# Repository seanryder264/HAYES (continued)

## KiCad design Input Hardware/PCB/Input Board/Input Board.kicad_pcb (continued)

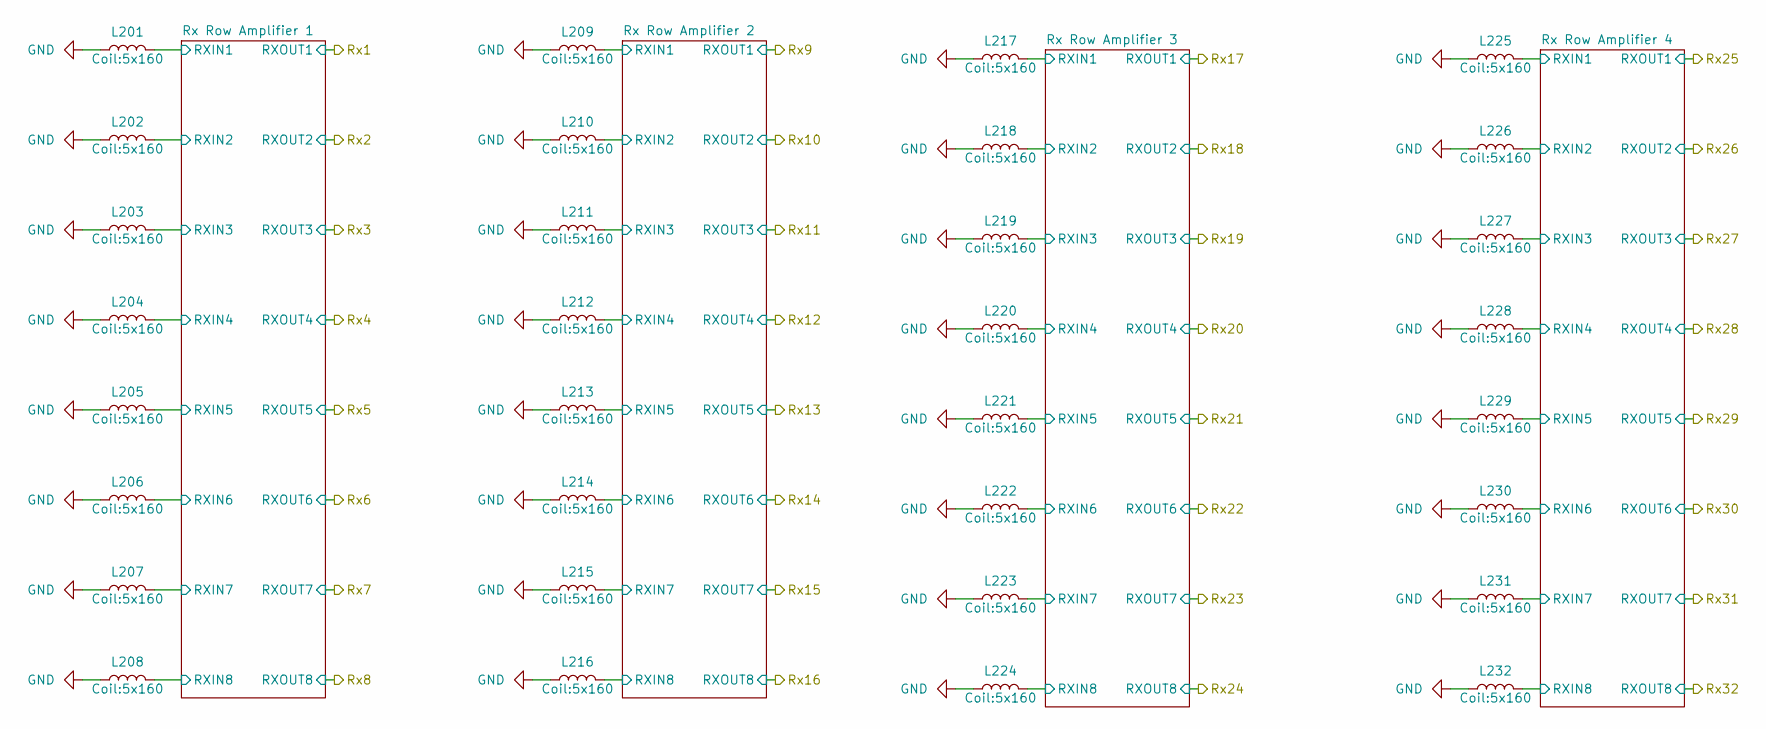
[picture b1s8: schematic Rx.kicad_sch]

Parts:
L201, L202, L203, L204, L205, L206, L207, L208, L209, L210, L211, L212, L213, L214, L215, L216, L217, L218, L219, L220, L221, L222, L223, L224, L225, L226, L227, L228, L229, L230, L231, L232: L; 5x160

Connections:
/Receiver Stage/Rx Row Amplifier 1/RXIN1: L201.2; also elsewhere on the board
/Receiver Stage/Rx Row Amplifier 1/RXIN2: L202.2; also elsewhere on the board
/Receiver Stage/Rx Row Amplifier 1/RXIN3: L203.2; also elsewhere on the board
/Receiver Stage/Rx Row Amplifier 1/RXIN4: L204.2; also elsewhere on the board
/Receiver Stage/Rx Row Amplifier 1/RXIN5: L205.2; also elsewhere on the board
/Receiver Stage/Rx Row Amplifier 1/RXIN6: L206.2; also elsewhere on the board
/Receiver Stage/Rx Row Amplifier 1/RXIN7: L207.2; also elsewhere on the board
/Receiver Stage/Rx Row Amplifier 1/RXIN8: L208.2; also elsewhere on the board
/Receiver Stage/Rx Row Amplifier 2/RXIN1: L209.2; also elsewhere on the board
/Receiver Stage/Rx Row Amplifier 2/RXIN2: L210.2; also elsewhere on the board
/Receiver Stage/Rx Row Amplifier 2/RXIN3: L211.2; also elsewhere on the board
/Receiver Stage/Rx Row Amplifier 2/RXIN4: L212.2; also elsewhere on the board
/Receiver Stage/Rx Row Amplifier 2/RXIN5: L213.2; also elsewhere on the board
/Receiver Stage/Rx Row Amplifier 2/RXIN6: L214.2; also elsewhere on the board
/Receiver Stage/Rx Row Amplifier 2/RXIN7: L215.2; also elsewhere on the board
/Receiver Stage/Rx Row Amplifier 2/RXIN8: L216.2; also elsewhere on the board
/Receiver Stage/Rx Row Amplifier 3/RXIN1: L217.2; also elsewhere on the board
/Receiver Stage/Rx Row Amplifier 3/RXIN2: L218.2; also elsewhere on the board
/Receiver Stage/Rx Row Amplifier 3/RXIN3: L219.2; also elsewhere on the board
/Receiver Stage/Rx Row Amplifier 3/RXIN4: L220.2; also elsewhere on the board
/Receiver Stage/Rx Row Amplifier 3/RXIN5: L221.2; also elsewhere on the board
/Receiver Stage/Rx Row Amplifier 3/RXIN6: L222.2; also elsewhere on the board
/Receiver Stage/Rx Row Amplifier 3/RXIN7: L223.2; also elsewhere on the board
/Receiver Stage/Rx Row Amplifier 3/RXIN8: L224.2; also elsewhere on the board
/Receiver Stage/Rx Row Amplifier 4/RXIN1: L225.2; also elsewhere on the board
/Receiver Stage/Rx Row Amplifier 4/RXIN2: L226.2; also elsewhere on the board
/Receiver Stage/Rx Row Amplifier 4/RXIN3: L227.2; also elsewhere on the board
/Receiver Stage/Rx Row Amplifier 4/RXIN4: L228.2; also elsewhere on the board
/Receiver Stage/Rx Row Amplifier 4/RXIN5: L229.2; also elsewhere on the board
/Receiver Stage/Rx Row Amplifier 4/RXIN6: L230.2; also elsewhere on the board
/Receiver Stage/Rx Row Amplifier 4/RXIN7: L231.2; also elsewhere on the board
/Receiver Stage/Rx Row Amplifier 4/RXIN8: L232.2; also elsewhere on the board

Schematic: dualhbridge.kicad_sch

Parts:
C1101, C1102, C1103, C1104, C1105: 100n; C_0603_1608Metric
U1101: 74HCS95; DHVQFN-16-1EP_2.5x3.5mm_P0.5mm_EP1x2mm
U1102, U1103, U1104, U1105: DRV8837; WSON-8-1EP_2x2mm_P0.5mm_EP0.9x1.6mm

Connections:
+5V: C1101.2, C1102.2, C1103.2, C1104.2, C1105.2, U1101.10 (~SRCLR), U1101.16 (VCC), U1102.1 (VM), U1102.8 (VCC), U1103.1 (VM), U1103.8 (VCC), U1104.1 (VM), U1104.8 (VCC), U1105.1 (VM), U1105.8 (VCC); also elsewhere on the board
/Measurement & Control/TX_RCLK: U1101.12 (RCLK); also elsewhere on the board
/Measurement & Control/TX_SDO: U1101.14 (SER); also elsewhere on the board
/Measurement & Control/TX_SRCLK: U1101.11 (SRCLK); also elsewhere on the board
/Transmit Coils/Dual H-Bridge 1/OUT1: U1102.2 (OUT1); also elsewhere on the board
/Transmit Coils/Dual H-Bridge 1/OUT2: U1102.3 (OUT2); also elsewhere on the board
/Transmit Coils/Dual H-Bridge 1/OUT3: U1103.2 (OUT1); also elsewhere on the board
/Transmit Coils/Dual H-Bridge 1/OUT4: U1103.3 (OUT2); also elsewhere on the board
/Transmit Coils/Dual H-Bridge 1/OUT5: U1104.2 (OUT1); also elsewhere on the board
/Transmit Coils/Dual H-Bridge 1/OUT6: U1104.3 (OUT2); also elsewhere on the board
/Transmit Coils/Dual H-Bridge 1/OUT7: U1105.2 (OUT1); also elsewhere on the board
/Transmit Coils/Dual H-Bridge 1/OUT8: U1105.3 (OUT2); also elsewhere on the board
/Transmit Coils/Dual H-Bridge 1/QH': U1101.9 (QH'); also elsewhere on the board
unnamed: U1101.15 (QA), U1102.6 (IN1)
unnamed: U1101.1 (QB), U1102.5 (IN2)
unnamed: U1101.2 (QC), U1103.6 (IN1)
unnamed: U1101.3 (QD), U1103.5 (IN2)
unnamed: U1101.4 (QE), U1104.6 (IN1)
unnamed: U1101.5 (QF), U1104.5 (IN2)
unnamed: U1101.6 (QG), U1105.6 (IN1)
unnamed: U1101.7 (QH), U1105.5 (IN2)

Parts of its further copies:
C1201, C1202, C1203, C1204, C1205, C1301, C1302, C1303, C1304, C1305, C1401, C1402, C1403, C1404, C1405: 100n; C_0603_1608Metric
U1201, U1301, U1401: 74HCS95; DHVQFN-16-1EP_2.5x3.5mm_P0.5mm_EP1x2mm
U1202, U1203, U1204, U1205, U1302, U1303, U1304, U1305, U1402, U1403, U1404, U1405: DRV8837; WSON-8-1EP_2x2mm_P0.5mm_EP0.9x1.6mm

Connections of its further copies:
+5V: C1201.2, C1202.2, C1203.2, C1204.2, C1205.2, C1301.2, C1302.2, C1303.2, C1304.2, C1305.2, C1401.2, C1402.2, C1403.2, C1404.2, C1405.2, U1201.10 (~SRCLR), U1201.16 (VCC), U1202.1 (VM), U1202.8 (VCC), U1203.1 (VM), U1203.8 (VCC), U1204.1 (VM), U1204.8 (VCC), U1205.1 (VM), U1205.8 (VCC), U1301.10 (~SRCLR), U1301.16 (VCC), U1302.1 (VM), U1302.8 (VCC), U1303.1 (VM), U1303.8 (VCC), U1304.1 (VM), U1304.8 (VCC), U1305.1 (VM), U1305.8 (VCC), U1401.10 (~SRCLR), U1401.16 (VCC), U1402.1 (VM), U1402.8 (VCC), U1403.1 (VM), U1403.8 (VCC), U1404.1 (VM), U1404.8 (VCC), U1405.1 (VM), U1405.8 (VCC); also elsewhere on the board
/Measurement & Control/TX_RCLK: U1201.12 (RCLK), U1301.12 (RCLK), U1401.12 (RCLK); also elsewhere on the board
/Measurement & Control/TX_SRCLK: U1201.11 (SRCLK), U1301.11 (SRCLK), U1401.11 (SRCLK); also elsewhere on the board
/Transmit Coils/Dual H-Bridge 1/QH': U1201.14 (SER); also elsewhere on the board
/Transmit Coils/Dual H-Bridge 2/OUT1: U1202.2 (OUT1); also elsewhere on the board
/Transmit Coils/Dual H-Bridge 2/OUT2: U1202.3 (OUT2); also elsewhere on the board
/Transmit Coils/Dual H-Bridge 2/OUT3: U1203.2 (OUT1); also elsewhere on the board
/Transmit Coils/Dual H-Bridge 2/OUT4: U1203.3 (OUT2); also elsewhere on the board
/Transmit Coils/Dual H-Bridge 2/OUT5: U1204.2 (OUT1); also elsewhere on the board
/Transmit Coils/Dual H-Bridge 2/OUT6: U1204.3 (OUT2); also elsewhere on the board
/Transmit Coils/Dual H-Bridge 2/OUT7: U1205.2 (OUT1); also elsewhere on the board
/Transmit Coils/Dual H-Bridge 2/OUT8: U1205.3 (OUT2); also elsewhere on the board
/Transmit Coils/Dual H-Bridge 3/OUT1: U1302.2 (OUT1); also elsewhere on the board
/Transmit Coils/Dual H-Bridge 3/OUT2: U1302.3 (OUT2); also elsewhere on the board
/Transmit Coils/Dual H-Bridge 3/OUT3: U1303.2 (OUT1); also elsewhere on the board
/Transmit Coils/Dual H-Bridge 3/OUT4: U1303.3 (OUT2); also elsewhere on the board
/Transmit Coils/Dual H-Bridge 3/OUT5: U1304.2 (OUT1); also elsewhere on the board
/Transmit Coils/Dual H-Bridge 3/OUT6: U1304.3 (OUT2); also elsewhere on the board
/Transmit Coils/Dual H-Bridge 3/OUT7: U1305.2 (OUT1); also elsewhere on the board
/Transmit Coils/Dual H-Bridge 3/OUT8: U1305.3 (OUT2); also elsewhere on the board
/Transmit Coils/Dual H-Bridge 3/QH': U1301.9 (QH'), U1401.14 (SER)
/Transmit Coils/Dual H-Bridge 4/OUT1: U1402.2 (OUT1); also elsewhere on the board
/Transmit Coils/Dual H-Bridge 4/OUT2: U1402.3 (OUT2); also elsewhere on the board
/Transmit Coils/Dual H-Bridge 4/OUT3: U1403.2 (OUT1); also elsewhere on the board
/Transmit Coils/Dual H-Bridge 4/OUT4: U1403.3 (OUT2); also elsewhere on the board
/Transmit Coils/Dual H-Bridge 4/OUT5: U1404.2 (OUT1); also elsewhere on the board
/Transmit Coils/Dual H-Bridge 4/OUT6: U1404.3 (OUT2); also elsewhere on the board
/Transmit Coils/Dual H-Bridge 4/OUT7: U1405.2 (OUT1); also elsewhere on the board
/Transmit Coils/Dual H-Bridge 4/OUT8: U1405.3 (OUT2); also elsewhere on the board
/Transmit Coils/Dual H-Bridge 4/QH&apos;: U1401.9 (QH')
/Transmit Coils/QH': U1201.9 (QH'), U1301.14 (SER)
unnamed: U1201.15 (QA), U1202.6 (IN1)
unnamed: U1201.1 (QB), U1202.5 (IN2)
unnamed: U1201.2 (QC), U1203.6 (IN1)
unnamed: U1201.3 (QD), U1203.5 (IN2)
unnamed: U1201.4 (QE), U1204.6 (IN1)
unnamed: U1201.5 (QF), U1204.5 (IN2)
unnamed: U1201.6 (QG), U1205.6 (IN1)
unnamed: U1201.7 (QH), U1205.5 (IN2)
unnamed: U1301.15 (QA), U1302.6 (IN1)
unnamed: U1301.1 (QB), U1302.5 (IN2)
unnamed: U1301.2 (QC), U1303.6 (IN1)
unnamed: U1301.3 (QD), U1303.5 (IN2)
unnamed: U1301.4 (QE), U1304.6 (IN1)
unnamed: U1301.5 (QF), U1304.5 (IN2)
unnamed: U1301.6 (QG), U1305.6 (IN1)
unnamed: U1301.7 (QH), U1305.5 (IN2)
unnamed: U1401.15 (QA), U1402.6 (IN1)
unnamed: U1401.1 (QB), U1402.5 (IN2)
unnamed: U1401.2 (QC), U1403.6 (IN1)
unnamed: U1401.3 (QD), U1403.5 (IN2)
unnamed: U1401.4 (QE), U1404.6 (IN1)
unnamed: U1401.5 (QF), U1404.5 (IN2)
unnamed: U1401.6 (QG), U1405.6 (IN1)
unnamed: U1401.7 (QH), U1405.5 (IN2)

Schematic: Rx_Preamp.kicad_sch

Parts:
C301, C302, C303, C304, C306, C307, C309, C310, C311, C312, C313, C314, C315, C316, C317, C318: 1.8n; C_0603_1608Metric
C305, C308: 100n; C_0603_1608Metric
R301, R302, R303, R304, R307, R308, R309, R310, R313, R314, R315, R316, R319, R320, R321, R322: 1k; R_0603_1608Metric
R305, R306, R311, R312, R317, R318, R323, R324: 15k; R_0603_1608Metric
U301, U302: TSV994; SOIC-14_3.9x8.7mm_P1.27mm

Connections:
1.65V: C303.2, C304.2, C309.2, C310.2, C313.2, C314.2, C317.2, C318.2, R301.1, R302.1, R307.1, R308.1, R313.1, R314.1, R319.1, R320.1; also elsewhere on the board
+3.3VA: C305.1, C308.1, U301.4 (V+), U302.4 (V+); also elsewhere on the board
/Mux & Amplifier 1/In1: R305.2, U301.1; also elsewhere on the board
/Mux & Amplifier 1/In2: R306.2, U301.7; also elsewhere on the board
/Mux & Amplifier 1/In3: R311.2, U301.8; also elsewhere on the board
/Mux & Amplifier 1/In4: R312.2, U301.14; also elsewhere on the board
/Mux & Amplifier 1/In5: R317.2, U302.1; also elsewhere on the board
/Mux & Amplifier 1/In6: R318.2, U302.7; also elsewhere on the board
/Mux & Amplifier 1/In7: R323.2, U302.8; also elsewhere on the board
/Mux & Amplifier 1/In8: R324.2, U302.14; also elsewhere on the board
/Receiver Stage/Rx Row Amplifier 1/RXIN1: C301.2; also elsewhere on the board
/Receiver Stage/Rx Row Amplifier 1/RXIN2: C302.2; also elsewhere on the board
/Receiver Stage/Rx Row Amplifier 1/RXIN3: C306.2; also elsewhere on the board
/Receiver Stage/Rx Row Amplifier 1/RXIN4: C307.2; also elsewhere on the board
/Receiver Stage/Rx Row Amplifier 1/RXIN5: C311.2; also elsewhere on the board
/Receiver Stage/Rx Row Amplifier 1/RXIN6: C312.2; also elsewhere on the board
/Receiver Stage/Rx Row Amplifier 1/RXIN7: C315.2; also elsewhere on the board
/Receiver Stage/Rx Row Amplifier 1/RXIN8: C316.2; also elsewhere on the board
unnamed: C303.1, R303.2
unnamed: C304.1, R304.2
unnamed: C309.1, R309.2
unnamed: C310.1, R310.2
unnamed: C313.1, R315.2
unnamed: C314.1, R316.2
unnamed: C317.1, R321.2
unnamed: C318.1, R322.2
unnamed: C301.1, R301.2, U301.3 (+)
unnamed: R303.1, R305.1, U301.2 (-)
unnamed: C302.1, R302.2, U301.5 (+)
unnamed: R304.1, R306.1, U301.6 (-)
unnamed: C306.1, R307.2, U301.10 (+)
unnamed: R309.1, R311.1, U301.9 (-)
unnamed: C307.1, R308.2, U301.12 (+)
unnamed: R310.1, R312.1, U301.13 (-)
unnamed: C311.1, R313.2, U302.3 (+)
unnamed: R315.1, R317.1, U302.2 (-)
unnamed: C312.1, R314.2, U302.5 (+)
unnamed: R316.1, R318.1, U302.6 (-)
unnamed: C315.1, R319.2, U302.10 (+)
unnamed: R321.1, R323.1, U302.9 (-)
unnamed: C316.1, R320.2, U302.12 (+)
unnamed: R322.1, R324.1, U302.13 (-)

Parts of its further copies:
C401, C402, C403, C404, C406, C407, C409, C410, C411, C412, C413, C414, C415, C416, C417, C418, C501, C502, C503, C504, C506, C507, C509, C510, C511, C512, C513, C514, C515, C516, C517, C518, C601, C602, C603, C604, C606, C607, C609, C610, C611, C612, C613, C614, C615, C616, C617, C618: 1.8n; C_0603_1608Metric
C405, C408, C505, C508, C605, C608: 100n; C_0603_1608Metric
R401, R402, R403, R404, R407, R408, R409, R410, R413, R414, R415, R416, R419, R420, R421, R422, R501, R502, R503, R504, R507, R508, R509, R510, R513, R514, R515, R516, R519, R520, R521, R522, R601, R602, R603, R604, R607, R608, R609, R610, R613, R614, R615, R616, R619, R620, R621, R622: 1k; R_0603_1608Metric
R405, R406, R411, R412, R417, R418, R423, R424, R505, R506, R511, R512, R517, R518, R523, R524, R605, R606, R611, R612, R617, R618, R623, R624: 15k; R_0603_1608Metric
U401, U402, U501, U502, U601, U602: TSV994; SOIC-14_3.9x8.7mm_P1.27mm

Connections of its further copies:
1.65V: C403.2, C404.2, C409.2, C410.2, C413.2, C414.2, C417.2, C418.2, C503.2, C504.2, C509.2, C510.2, C513.2, C514.2, C517.2, C518.2, C603.2, C604.2, C609.2, C610.2, C613.2, C614.2, C617.2, C618.2, R401.1, R402.1, R407.1, R408.1, R413.1, R414.1, R419.1, R420.1, R501.1, R502.1, R507.1, R508.1, R513.1, R514.1, R519.1, R520.1, R601.1, R602.1, R607.1, R608.1, R613.1, R614.1, R619.1, R620.1; also elsewhere on the board
+3.3VA: C405.1, C408.1, C505.1, C508.1, C605.1, C608.1, U401.4 (V+), U402.4 (V+), U501.4 (V+), U502.4 (V+), U601.4 (V+), U602.4 (V+); also elsewhere on the board
/Mux & Amplifier 1/In9: R405.2, U401.1; also elsewhere on the board
/Mux & Amplifier 1/In10: R406.2, U401.7; also elsewhere on the board
/Mux & Amplifier 1/In11: R411.2, U401.8; also elsewhere on the board
/Mux & Amplifier 1/In12: R412.2, U401.14; also elsewhere on the board
/Mux & Amplifier 1/In13: R417.2, U402.1; also elsewhere on the board
/Mux & Amplifier 1/In14: R418.2, U402.7; also elsewhere on the board
/Mux & Amplifier 1/In15: R423.2, U402.8; also elsewhere on the board
/Mux & Amplifier 1/In16: R424.2, U402.14; also elsewhere on the board
/Mux & Amplifier 2/In1: R505.2, U501.1; also elsewhere on the board
/Mux & Amplifier 2/In2: R506.2, U501.7; also elsewhere on the board
/Mux & Amplifier 2/In3: R511.2, U501.8; also elsewhere on the board
/Mux & Amplifier 2/In4: R512.2, U501.14; also elsewhere on the board
/Mux & Amplifier 2/In5: R517.2, U502.1; also elsewhere on the board
/Mux & Amplifier 2/In6: R518.2, U502.7; also elsewhere on the board
/Mux & Amplifier 2/In7: R523.2, U502.8; also elsewhere on the board
/Mux & Amplifier 2/In8: R524.2, U502.14; also elsewhere on the board
/Mux & Amplifier 2/In9: R605.2, U601.1; also elsewhere on the board
/Mux & Amplifier 2/In10: R606.2, U601.7; also elsewhere on the board
/Mux & Amplifier 2/In11: R611.2, U601.8; also elsewhere on the board
/Mux & Amplifier 2/In12: R612.2, U601.14; also elsewhere on the board
/Mux & Amplifier 2/In13: R617.2, U602.1; also elsewhere on the board
/Mux & Amplifier 2/In14: R618.2, U602.7; also elsewhere on the board
/Mux & Amplifier 2/In15: R623.2, U602.8; also elsewhere on the board
/Mux & Amplifier 2/In16: R624.2, U602.14; also elsewhere on the board
/Receiver Stage/Rx Row Amplifier 2/RXIN1: C401.2; also elsewhere on the board
/Receiver Stage/Rx Row Amplifier 2/RXIN2: C402.2; also elsewhere on the board
/Receiver Stage/Rx Row Amplifier 2/RXIN3: C406.2; also elsewhere on the board
/Receiver Stage/Rx Row Amplifier 2/RXIN4: C407.2; also elsewhere on the board
/Receiver Stage/Rx Row Amplifier 2/RXIN5: C411.2; also elsewhere on the board
/Receiver Stage/Rx Row Amplifier 2/RXIN6: C412.2; also elsewhere on the board
/Receiver Stage/Rx Row Amplifier 2/RXIN7: C415.2; also elsewhere on the board
/Receiver Stage/Rx Row Amplifier 2/RXIN8: C416.2; also elsewhere on the board
/Receiver Stage/Rx Row Amplifier 3/RXIN1: C501.2; also elsewhere on the board
/Receiver Stage/Rx Row Amplifier 3/RXIN2: C502.2; also elsewhere on the board
/Receiver Stage/Rx Row Amplifier 3/RXIN3: C506.2; also elsewhere on the board
/Receiver Stage/Rx Row Amplifier 3/RXIN4: C507.2; also elsewhere on the board
/Receiver Stage/Rx Row Amplifier 3/RXIN5: C511.2; also elsewhere on the board
/Receiver Stage/Rx Row Amplifier 3/RXIN6: C512.2; also elsewhere on the board
/Receiver Stage/Rx Row Amplifier 3/RXIN7: C515.2; also elsewhere on the board
/Receiver Stage/Rx Row Amplifier 3/RXIN8: C516.2; also elsewhere on the board
/Receiver Stage/Rx Row Amplifier 4/RXIN1: C601.2; also elsewhere on the board
/Receiver Stage/Rx Row Amplifier 4/RXIN2: C602.2; also elsewhere on the board
/Receiver Stage/Rx Row Amplifier 4/RXIN3: C606.2; also elsewhere on the board
/Receiver Stage/Rx Row Amplifier 4/RXIN4: C607.2; also elsewhere on the board
/Receiver Stage/Rx Row Amplifier 4/RXIN5: C611.2; also elsewhere on the board
/Receiver Stage/Rx Row Amplifier 4/RXIN6: C612.2; also elsewhere on the board
/Receiver Stage/Rx Row Amplifier 4/RXIN7: C615.2; also elsewhere on the board
/Receiver Stage/Rx Row Amplifier 4/RXIN8: C616.2; also elsewhere on the board
unnamed: C403.1, R403.2
unnamed: C404.1, R404.2
unnamed: C409.1, R409.2
unnamed: C410.1, R410.2
unnamed: C413.1, R415.2
unnamed: C414.1, R416.2
unnamed: C417.1, R421.2
unnamed: C418.1, R422.2
unnamed: C503.1, R503.2
unnamed: C504.1, R504.2
unnamed: C509.1, R509.2
unnamed: C510.1, R510.2
unnamed: C513.1, R515.2
unnamed: C514.1, R516.2
unnamed: C517.1, R521.2
unnamed: C518.1, R522.2
unnamed: C603.1, R603.2
unnamed: C604.1, R604.2
unnamed: C609.1, R609.2
unnamed: C610.1, R610.2
unnamed: C613.1, R615.2
unnamed: C614.1, R616.2
unnamed: C617.1, R621.2
unnamed: C618.1, R622.2
unnamed: C401.1, R401.2, U401.3 (+)
unnamed: R403.1, R405.1, U401.2 (-)
unnamed: C402.1, R402.2, U401.5 (+)
unnamed: R404.1, R406.1, U401.6 (-)
unnamed: C406.1, R407.2, U401.10 (+)
unnamed: R409.1, R411.1, U401.9 (-)
unnamed: C407.1, R408.2, U401.12 (+)
unnamed: R410.1, R412.1, U401.13 (-)
unnamed: C411.1, R413.2, U402.3 (+)
unnamed: R415.1, R417.1, U402.2 (-)
unnamed: C412.1, R414.2, U402.5 (+)
unnamed: R416.1, R418.1, U402.6 (-)
unnamed: C415.1, R419.2, U402.10 (+)
unnamed: R421.1, R423.1, U402.9 (-)
unnamed: C416.1, R420.2, U402.12 (+)
unnamed: R422.1, R424.1, U402.13 (-)
unnamed: C501.1, R501.2, U501.3 (+)
unnamed: R503.1, R505.1, U501.2 (-)
unnamed: C502.1, R502.2, U501.5 (+)
unnamed: R504.1, R506.1, U501.6 (-)
unnamed: C506.1, R507.2, U501.10 (+)
unnamed: R509.1, R511.1, U501.9 (-)
unnamed: C507.1, R508.2, U501.12 (+)
unnamed: R510.1, R512.1, U501.13 (-)
unnamed: C511.1, R513.2, U502.3 (+)
unnamed: R515.1, R517.1, U502.2 (-)
unnamed: C512.1, R514.2, U502.5 (+)
unnamed: R516.1, R518.1, U502.6 (-)
unnamed: C515.1, R519.2, U502.10 (+)
unnamed: R521.1, R523.1, U502.9 (-)
unnamed: C516.1, R520.2, U502.12 (+)
unnamed: R522.1, R524.1, U502.13 (-)
unnamed: C601.1, R601.2, U601.3 (+)
unnamed: R603.1, R605.1, U601.2 (-)
unnamed: C602.1, R602.2, U601.5 (+)
unnamed: R604.1, R606.1, U601.6 (-)
unnamed: C606.1, R607.2, U601.10 (+)
unnamed: R609.1, R611.1, U601.9 (-)
unnamed: C607.1, R608.2, U601.12 (+)
unnamed: R610.1, R612.1, U601.13 (-)
unnamed: C611.1, R613.2, U602.3 (+)
unnamed: R615.1, R617.1, U602.2 (-)
unnamed: C612.1, R614.2, U602.5 (+)
unnamed: R616.1, R618.1, U602.6 (-)
unnamed: C615.1, R619.2, U602.10 (+)
unnamed: R621.1, R623.1, U602.9 (-)
unnamed: C616.1, R620.2, U602.12 (+)
unnamed: R622.1, R624.1, U602.13 (-)

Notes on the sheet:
OPAMP NOT ALWAYS STABLE
TSV994
×17.7 @1MHz Gain slightly less to preserve bandwidth
This is almost certainly wrong look at the transfer functions also sims rely on a slight approximation of this opamp so may actually be completley incorrect

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
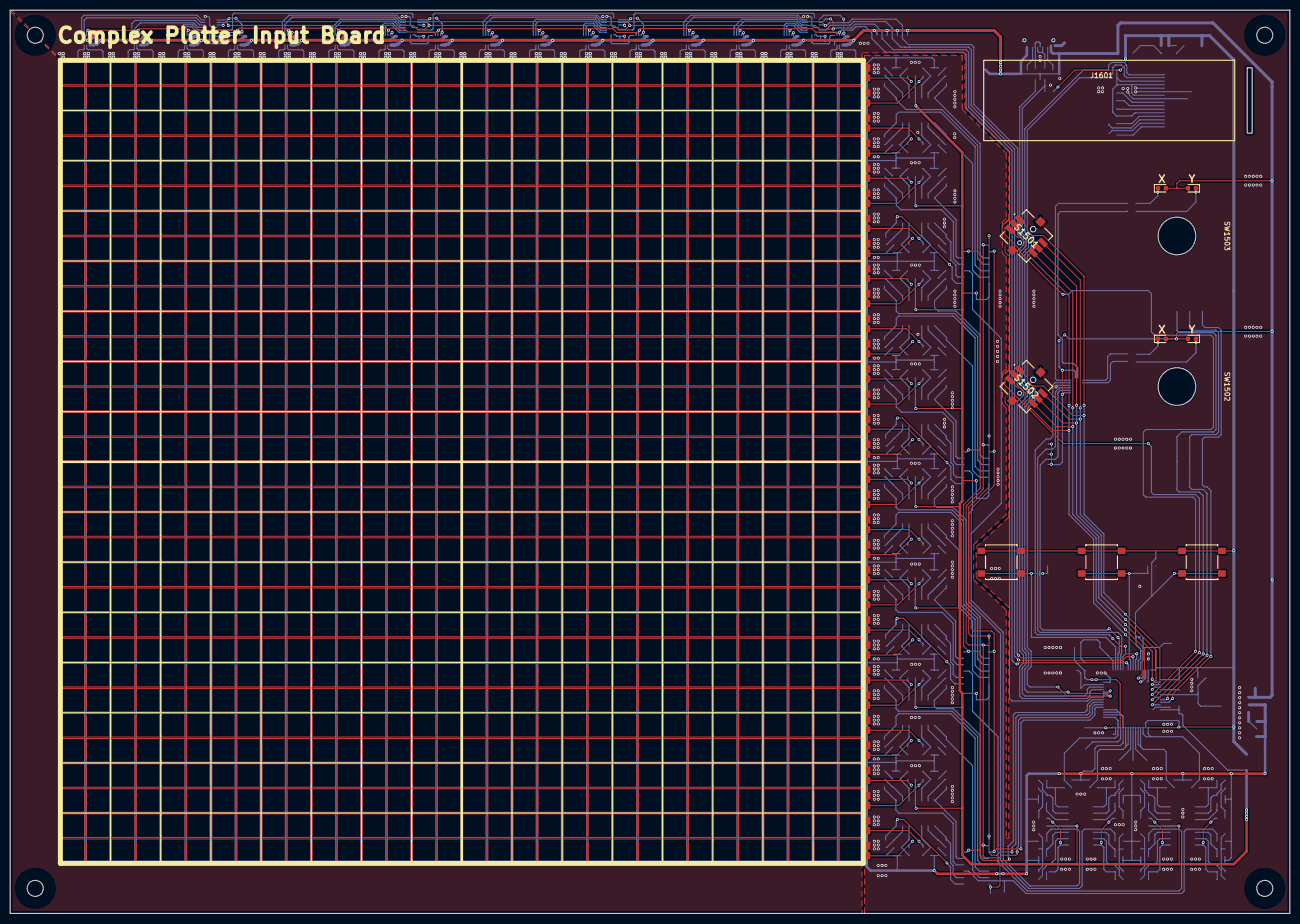
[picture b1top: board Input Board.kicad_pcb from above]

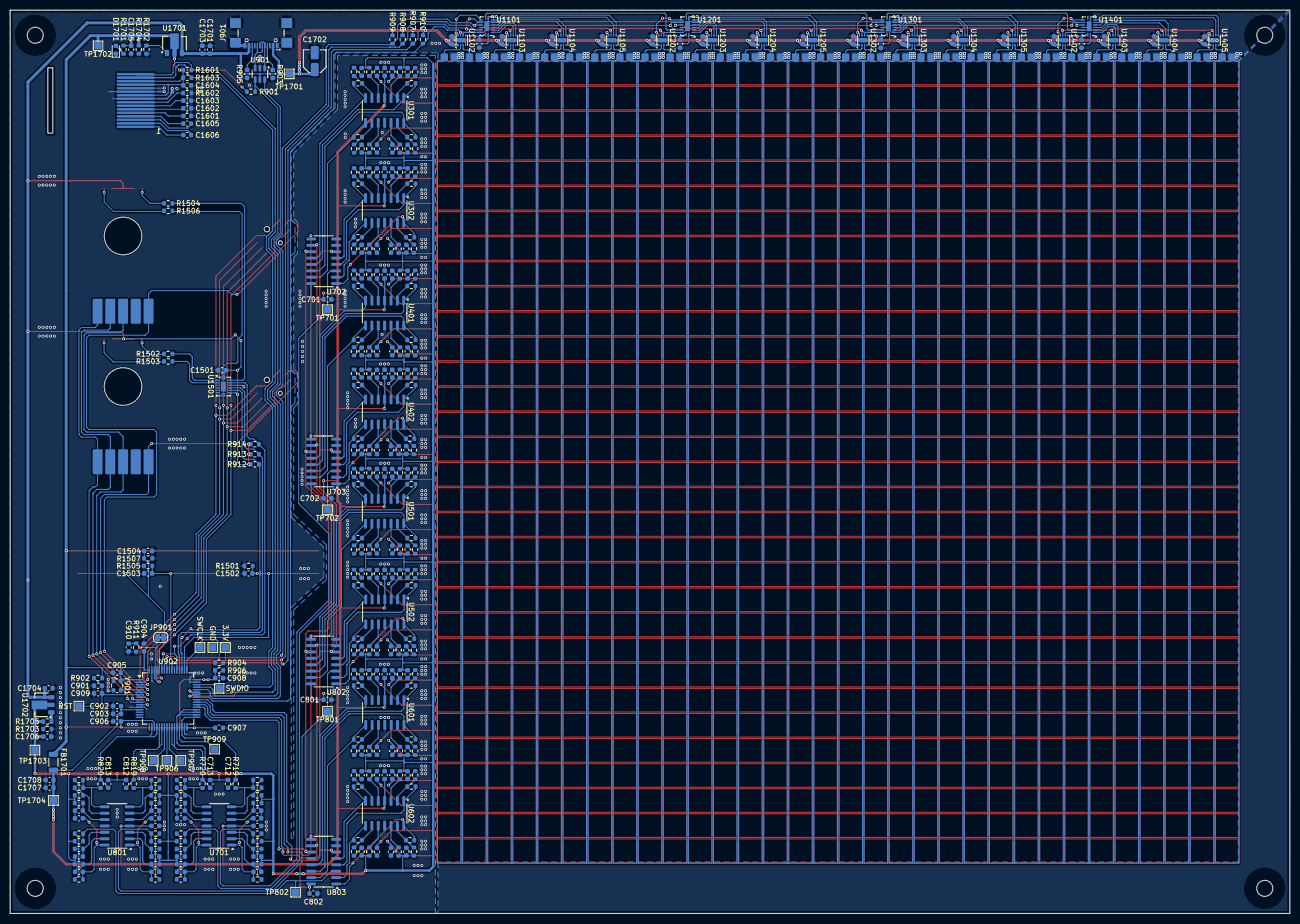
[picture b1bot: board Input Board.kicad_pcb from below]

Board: 2 copper layers, 255.0 x 180.0 mm, 452 parts (404 on the bottom side), 331 nets.

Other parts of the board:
R914: 10k; R_0603_1608Metric
R1502, R1504: 220; R_0603_1608Metric
TP909: TestPoint; TestPoint_Pad_1.5x1.5mm

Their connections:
+5V: R914.1; also elsewhere on the board
unnamed 280: TP909.1; also elsewhere on the board

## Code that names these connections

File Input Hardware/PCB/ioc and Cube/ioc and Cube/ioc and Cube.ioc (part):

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Mcu.Name=STM32F303R(B-C)Tx
Mcu.Package=LQFP64
Mcu.UserName=STM32F303RBTx
PA10.GPIOParameters=GPIO_Label
PA10.GPIO_Label=OLED_SDA
PA10.Mode=I2C
PA10.Signal=I2C2_SDA
PA11.Mode=Device
PA11.Signal=USB_DM
PA12.Mode=Device
PA12.Signal=USB_DP
PA13.Mode=Serial_Wire
PA13.Signal=SYS_JTMS-SWDIO
PA14.Mode=Serial_Wire
PA14.Signal=SYS_JTCK-SWCLK
PA15.GPIOParameters=GPIO_Label
PA15.GPIO_Label=PUSH_1
PA15.Signal=GPIO_Input
PA4.GPIOParameters=GPIO_Label
PA4.GPIO_Label=RX1_COMP
PA4.Mode=INM
PA4.Signal=COMP3_INM
PA5.GPIOParameters=GPIO_Label
PA5.GPIO_Label=RX3_COMP
PA5.Mode=INM
PA5.Signal=COMP5_INM
PA6.GPIOParameters=GPIO_Label
PA6.GPIO_Label=RX3_ADC
PA6.Mode=IN3-Single-Ended
PA6.Signal=ADC2_IN3
PA7.GPIOParameters=GPIO_Label
PA7.GPIO_Label=TP908
PA7.Signal=GPIO_Output
PA8.GPIOParameters=GPIO_Label
PA8.GPIO_Label=TX_SLEEP
PA8.Signal=GPIO_Output
PA9.GPIOParameters=GPIO_Label
PA9.GPIO_Label=OLED_SCL
PA9.Mode=I2C
PA9.Signal=I2C2_SCL
PB0.GPIOParameters=GPIO_Label
PB0.GPIO_Label=RX2_COMP
PB0.Mode=INP
PB0.Signal=COMP4_INP
PB1.GPIOParameters=GPIO_Label
PB1.GPIO_Label=RX2_ADC
PB1.Mode=IN1-Single-Ended
PB1.Signal=ADC3_IN1
PB10.GPIOParameters=GPIO_Label
PB10.GPIO_Label=TP909
PB10.Signal=GPIO_Output
PB11.GPIOParameters=GPIO_Label
PB11.GPIO_Label=RX4_COMP
PB11.Mode=INP
PB11.Signal=COMP6_INP
PB12.GPIOParameters=GPIO_Label
PB12.GPIO_Label=RX4_ADC
PB12.Mode=IN3-Single-Ended
PB12.Signal=ADC4_IN3
PB13.GPIOParameters=GPIO_Label
PB13.GPIO_Label=VREF
PB13.Mode=INP
PB13.Signal=COMP5_INP
PB14.GPIOParameters=GPIO_Label
PB14.GPIO_Label=VREF
PB14.Mode=INP
PB14.Signal=COMP3_INP
PB15.GPIOParameters=GPIO_Label
PB15.GPIO_Label=VREF
PB15.Mode=INM
PB15.Signal=COMP6_INM
PB2.GPIOParameters=GPIO_Label
PB2.GPIO_Label=VREF
PB2.Mode=INM
PB2.Signal=COMP4_INM
PB3.GPIOParameters=GPIO_Label
PB3.GPIO_Label=TX_CLK
PB3.Mode=TX_Only_Simplex_Unidirect_Master
PB3.Signal=SPI1_SCK
PB4.GPIOParameters=GPIO_Label
PB4.GPIO_Label=PUSH_2
PB4.Signal=GPIO_Output
PB5.GPIOParameters=GPIO_Label
PB5.GPIO_Label=TX_MOSI
PB5.Mode=TX_Only_Simplex_Unidirect_Master
PB5.Signal=SPI1_MOSI
PB6.GPIOParameters=GPIO_Label
PB6.GPIO_Label=TX_RCLK
PB6.Signal=GPIO_Output
PB7.GPIOParameters=GPIO_Label
PB7.GPIO_Label=PUSH_3
PB7.Signal=GPIO_Input
PB8.GPIOParameters=GPIO_Label
PB8.GPIO_Label=OFFSET_UP
PB8.Signal=GPIO_Input
PB9.GPIOParameters=GPIO_Label
PB9.GPIO_Label=OFFSET_DOWN
PB9.Signal=GPIO_Input
PC0.GPIOParameters=GPIO_Label
PC0.GPIO_Label=OUTPUT_COM
PC0.Signal=GPIO_Output
PC1.GPIOParameters=GPIO_Label
PC1.GPIO_Label=SCALE_B
PC1.Signal=GPIO_Input
PC10.GPIOParameters=GPIO_Label
PC10.GPIO_Label=UI_SCK
PC10.Mode=TX_Only_Simplex_Unidirect_Master
PC10.Signal=SPI3_SCK
PC11.GPIOParameters=GPIO_Label
PC11.GPIO_Label=UI_RCLK
PC11.Signal=GPIO_Output
PC12.GPIOParameters=GPIO_Label
PC12.GPIO_Label=UI_MOSI
PC12.Mode=TX_Only_Simplex_Unidirect_Master
PC12.Signal=SPI3_MOSI
PC13.GPIOParameters=GPIO_Label
PC13.GPIO_Label=OFFSET_CENTER
PC13.Signal=GPIO_Input
PC14-OSC32_IN.GPIOParameters=GPIO_Label
PC14-OSC32_IN.GPIO_Label=OFFSET_RIGHT
PC14-OSC32_IN.Signal=GPIO_Input
PC15-OSC32_OUT.GPIOParameters=GPIO_Label
PC15-OSC32_OUT.GPIO_Label=OFFSET_UP
PC15-OSC32_OUT.Signal=GPIO_Input
PC2.GPIOParameters=GPIO_Label
PC2.GPIO_Label=SCALE_A
PC2.Signal=GPIO_Input
PC3.GPIOParameters=GPIO_Label
PC3.GPIO_Label=SCALE_PUSH
PC3.Signal=GPIO_Input
PC4.GPIOParameters=GPIO_Label
PC4.GPIO_Label=TP906
PC4.Signal=GPIO_Output
PC5.GPIOParameters=GPIO_Label
PC5.GPIO_Label=TP907
PC5.Signal=GPIO_Output
PC6.GPIOParameters=GPIO_Label
PC6.GPIO_Label=MUX_A
PC6.Signal=GPIO_Output
PC7.GPIOParameters=GPIO_Label
PC7.GPIO_Label=MUX_B
PC7.Signal=GPIO_Output
PC8.GPIOParameters=GPIO_Label
PC8.GPIO_Label=MUX_C
PC8.Signal=GPIO_Output
PC9.GPIOParameters=GPIO_Label
PC9.GPIO_Label=MUX_INHIBIT
PC9.Signal=GPIO_Output
PF0-OSC_IN.Mode=HSE-External-Clock-Source
PF0-OSC_IN.Signal=RCC_OSC_IN
PF1-OSC_OUT.GPIOParameters=GPIO_Label
PF1-OSC_OUT.GPIO_Label=INPUT_COM
PF1-OSC_OUT.Signal=GPIO_Output
PF4.GPIOParameters=GPIO_Label
PF4.GPIO_Label=RX1_ADC
PF4.Mode=IN5-Single-Ended
PF4.Signal=ADC1_IN5
RCC.HSEPLLFreq_Value=8000000
RCC.HSE_VALUE=16000000
RCC.SYSCLKFreq_VALUE=72000000
RCC.SYSCLKSourceVirtual=RCC_SYSCLKSOURCE_PLLCLK
board=custom

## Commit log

2025-05-19 Fixed README.md
2025-05-19 basic outline of project plan
2025-05-19 formatting
2025-05-19 reformatted and added group member roles
2025-05-19 one change
2025-05-19 reformatting
2025-05-19 remove one thing
2025-05-20 interim presentation
2025-05-23 Create Input Board Project
2025-05-23 Generate Schematic
2025-05-23 Update Schematic
2025-05-23 Progress
2025-05-23 Fix Name
2025-05-24 said hello
2025-05-24 WEEEE
2025-05-24 uC Pin Assignment
2025-05-24 Power Board, Row amplifier setup etc
2025-05-24 Assign Analogue pins
2025-05-24 Reminder
2025-05-25 More pin assignments
2025-05-25 Fix merge error
2025-05-25 Revert "Fix merge error"
    This reverts commit d15345406901b9267cf586c177783854638d16cb.
2025-05-25 Revert "Merge branch 'main' of https://github.com/seanryder264/HAYES"
    This reverts commit bd795aa78e7b7049f2eb147f65c5fdd388d288f7, reversing
    changes made to 52c69ad61d85eaec29fd6b5b9781512ece56f4ea.
2025-05-25 FIX EVERYTHING
    I hope
2025-05-25 Redo this one
2025-05-25 integrate
2025-05-25 test commit and minor updates
2025-05-25 explosion 💥
2025-05-25 Modify preamp
2025-05-25 more fixes
2025-05-26 end me
2025-05-26 fodda
2025-05-26 opamp symbol
2025-05-26 Create Display Footprint
2025-05-26 Display first attempt
2025-05-26 spices
2025-05-26 more spices for row amp/adc bandpass amp
2025-05-26 adc bandpass amp and rootpage update
2025-05-26 minor changes
2025-05-26 row amp fixes and spice fixes
2025-05-26 Add lib for ts12
2025-05-26 Display and input update
2025-05-26 clean mux
2025-05-26 sims again
2025-05-26 kicad fix
2025-05-26 help
2025-05-26 input encoder and LEDs
2025-05-26 minor filter changes
2025-05-26 Add footprints
2025-05-26 More footprints
2025-05-26 created writup doc
2025-05-26 image upload and test
2025-05-26 paint diagram update
2025-05-26 minor
2025-05-26 i am braindead
2025-05-26 deleted a few things
2025-05-26 gitignore
2025-05-26 trying to get the simulation running
2025-05-26 Encoder Footprint
2025-05-26 Footprints
2025-05-26 images and pcb stuff
2025-05-26 Revert "conflict resolution"
    This reverts commit e2196486344c2f16c0f4e50e55e8bad7e306dbb3, reversing
    changes made to 6978c7447e140ee759e19aaebffdac22097ec1b9.
2025-05-26 Revert "images and pcb stuff"
    This reverts commit 6978c7447e140ee759e19aaebffdac22097ec1b9.
2025-05-26 still fucking up the repo
2025-05-26 should be back together now sorry about that
2025-05-26 fixed some errors in pixel_generator
2025-05-26 stmcube model and fixes
2025-05-26 writeup
2025-05-26 minor (sorry for commit spam)
2025-05-26 Fix footprints
2025-05-26 Fix files idc
2025-05-26 readd footprint
2025-05-26 at least it makes an image now
2025-05-26 more fodda
2025-05-26 full signal path sim
2025-05-26 not sure why its looking like that but seperated the image builder
2025-05-26 bedtime
2025-05-27 Layout
2025-05-27 Change topology
2025-05-27 remove image
2025-05-27 Revert "Update Input Board.kicad_pcb"
    This reverts commit fb32d5723672540be1a249144716d437570d2cea.
2025-05-27 coord_gen
2025-05-27 not working but structure layed out
2025-05-27 Filter Amplifier Layout
2025-05-27 driver circuits without conflicting changes
2025-05-27 Analogue layout
2025-05-27 driver and root page updates
2025-05-27 Revert "driver and root page updates"
    This reverts commit 54e272777a4dc0dc5d2e3cf73da3d3a01278b96a.
2025-05-27 driver format update
2025-05-27 Fix Sheet Numbers
2025-05-27 Layout Progress
2025-05-27 sims and other crap
2025-05-27 package type change
2025-05-27 Multiplier added
2025-05-27 comparison cpp script written and tested
2025-05-28 made a make file for comparison
2025-05-28 changed contour lines
2025-05-28 changed up contour lines again
2025-05-28 added grid lines
2025-05-28 Schematic Cleanup
2025-05-28 Trace Cleanup
2025-05-28 USB & OLED wiring
2025-05-28 finished the pipeline but i dont think image generation works
2025-05-28 made quick video simulation, may need to change settings for personal use, will improve
2025-05-28 file addition
2025-05-28 minor schematic changes and value assignment
2025-05-28 minor layout changes
2025-05-28 resistor value changes
2025-05-28 opamp part changes
2025-05-28 Fix opamp name
2025-05-28 Fixed Switches
2025-05-28 add bias resistor, fix LED polarity
2025-05-28 sims and Cube error resolution
2025-05-28 rtl began
2025-05-28 README Update and testbench one added
2025-05-28 Plan updated
2025-05-28 sleep pin rewire
2025-05-28 add TX sleep
2025-05-28 Final Layout
2025-05-28 Production Files
2025-05-29 RTL: Function evaluator added
2025-05-29 Added square_sum.v
2025-05-29 f(z)=z coloured
2025-05-29 two zeros
2025-05-30 function evaluation added
2025-05-31 trying to sort new layout
2025-05-31 directory cleaned up
2025-05-31 Structure for Log based calculation added
2025-05-31 its making something
2025-05-31 initial phase pipeline implemented
2025-05-31 Few syntax bugs fixed
2025-06-01 Some errors fixed
2025-06-01 yay its working for phase with poles
2025-06-01 need to fix some stuff with rgb but otherwise working
2025-06-01 fixed phase -> rgb
2025-06-01 phase at 45 deg fixed
2025-06-01 kinda got magnitude working
2025-06-01 Initial Aadin Test Running
2025-06-01 doubled to resolution
2025-06-02 4K lol
2025-06-02 matched
2025-06-02 Update Presentation Link
2025-06-02 Simple started
2025-06-03 Cube updates
2025-06-03 CubeIDE file creation
2025-06-03 CubeIDE incomplete debug program
2025-06-03 CubeIDE and CubeMX updates and refactor
2025-06-03 Cube final error resolution and project creation
2025-06-03 crap shift register interface
2025-06-04 Resonator files, cleanup
2025-06-04 8MHz clock config update
2025-06-05 freertos enable
2025-06-05 ngl you were right cube is totally unusable
2025-06-05 cube is Crap
2025-06-05 platformio
2025-06-05 Fix platformio.ini
2025-06-05 filter updates to eliminate 140kHz
2025-06-05 more sims
2025-06-06 Firmware project
2025-06-06 Build out structure
2025-06-06 Ready to hang myself
2025-06-06 change colour_app to handle different word lengths inputs and valid and ready flags
2025-06-08 Create FPGA Adaptation
2025-06-08 added current working fpga adaptation
2025-06-08 added adaptation
2025-06-08 made a lot of changes
2025-06-08 dont know what these changes are
2025-06-09 Measurement Progress
2025-06-09 save
2025-06-09 verilator changes
2025-06-09 trying to get sim working
2025-06-09 ahhh
2025-06-09 yay it works
2025-06-09 back to cube
2025-06-09 USB and OLED code
2025-06-09 LED and shift register code
2025-06-11 UI (LEDs, dpads, rotaries, buttons)
2025-06-12 minor cosmetic
2025-06-12 my eyes are going square
2025-06-12 Move to PlatformIO
    Cube makes me sad
2025-06-13 Top 1/4 positioning!!!!
2025-06-14 working mag
2025-06-14 Full board detection
2025-06-14 fixed simulation
2025-06-14 reduced lut
2025-06-15 comparison
